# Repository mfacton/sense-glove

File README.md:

# sense-glove
Position Sensing Glove

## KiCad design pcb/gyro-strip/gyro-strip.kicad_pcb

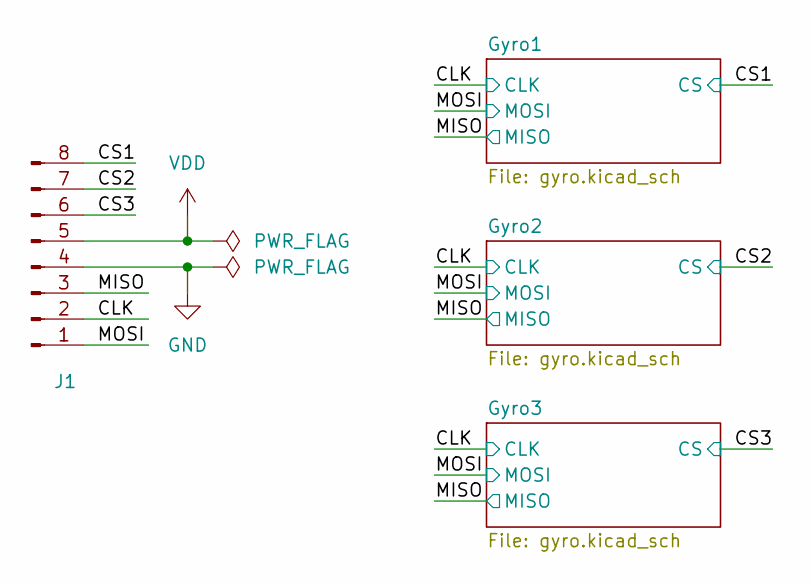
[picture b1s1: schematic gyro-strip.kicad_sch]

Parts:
J1: Conn_01x08_Pin; FPC_8P_P0.5mm

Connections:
/CLK: J1.2; also elsewhere on the board
/CS1: J1.8; also elsewhere on the board
/CS2: J1.7; also elsewhere on the board
/CS3: J1.6; also elsewhere on the board
/MISO: J1.3; also elsewhere on the board
/MOSI: J1.1; also elsewhere on the board
GND: J1.4; also elsewhere on the board
VDD: J1.5; also elsewhere on the board

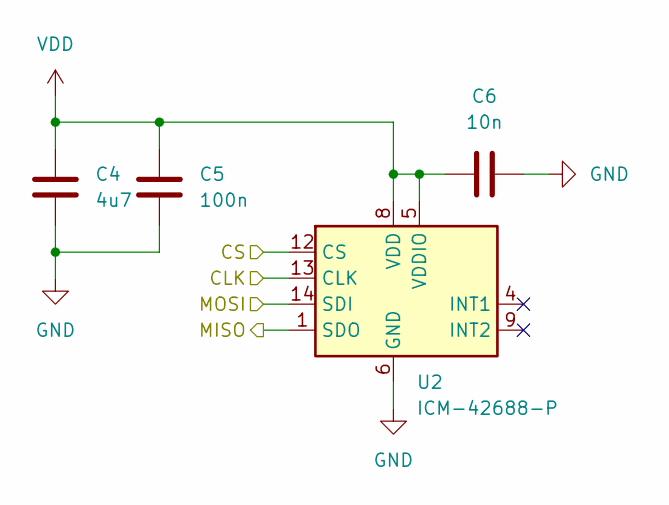
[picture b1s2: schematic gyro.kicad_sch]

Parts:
C4: 4u7; C_0402_1005Metric; LCSC C23733
C5: 100n; C_0402_1005Metric; LCSC C1525
C6: 10n; C_0402_1005Metric; LCSC C15195
U2: ICM-42688-P; LGA-14_3x2.5mm_P0.5mm_LayoutBorder3x4y; LCSC C1850418

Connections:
/CLK: U2.13 (CLK); also elsewhere on the board
/CS2: U2.12 (CS); also elsewhere on the board
/MISO: U2.1 (SDO); also elsewhere on the board
/MOSI: U2.14 (SDI); also elsewhere on the board
GND: C4.2, C5.2, C6.2, U2.6 (GND), U2.7 (RESV), U2.11 (RESV); also elsewhere on the board
VDD: C4.1, C5.1, C6.1, U2.5 (VDDIO), U2.8 (VDD); also elsewhere on the board

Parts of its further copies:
C1, C7: 4u7; C_0402_1005Metric; LCSC C23733
C2, C8: 100n; C_0402_1005Metric; LCSC C1525
C3, C9: 10n; C_0402_1005Metric; LCSC C15195
U1, U3: ICM-42688-P; LGA-14_3x2.5mm_P0.5mm_LayoutBorder3x4y; LCSC C1850418

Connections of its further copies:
/CLK: U1.13 (CLK), U3.13 (CLK); also elsewhere on the board
/CS1: U1.12 (CS); also elsewhere on the board
/CS3: U3.12 (CS); also elsewhere on the board
/MISO: U1.1 (SDO), U3.1 (SDO); also elsewhere on the board
/MOSI: U1.14 (SDI), U3.14 (SDI); also elsewhere on the board
GND: C1.2, C2.2, C3.2, C7.2, C8.2, C9.2, U1.6 (GND), U1.7 (RESV), U1.11 (RESV), U3.6 (GND), U3.7 (RESV), U3.11 (RESV); also elsewhere on the board
VDD: C1.1, C2.1, C3.1, C7.1, C8.1, C9.1, U1.5 (VDDIO), U1.8 (VDD), U3.5 (VDDIO), U3.8 (VDD); also elsewhere on the board

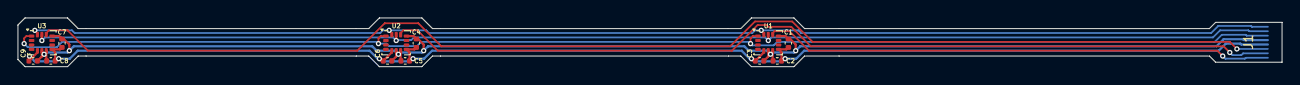
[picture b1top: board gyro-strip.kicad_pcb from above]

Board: 2 copper layers, 142.7 x 5.5 mm, 13 parts (0 on the bottom side), 8 nets.

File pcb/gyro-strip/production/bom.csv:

Designator,Footprint,Quantity,Value,LCSC Part #
"C1, C4, C7",0402,3,4u7,C23733
"C2, C5, C8",0402,3,100n,C1525
"C3, C6, C9",0402,3,10n,C15195
J1,FPC_8P_P0.5mm,1,Conn_01x08_Pin,
"U1, U2, U3",LGA-14_3x2.5mm_P0.5mm_LayoutBorder3x4y,3,ICM-42688-P,C1850418

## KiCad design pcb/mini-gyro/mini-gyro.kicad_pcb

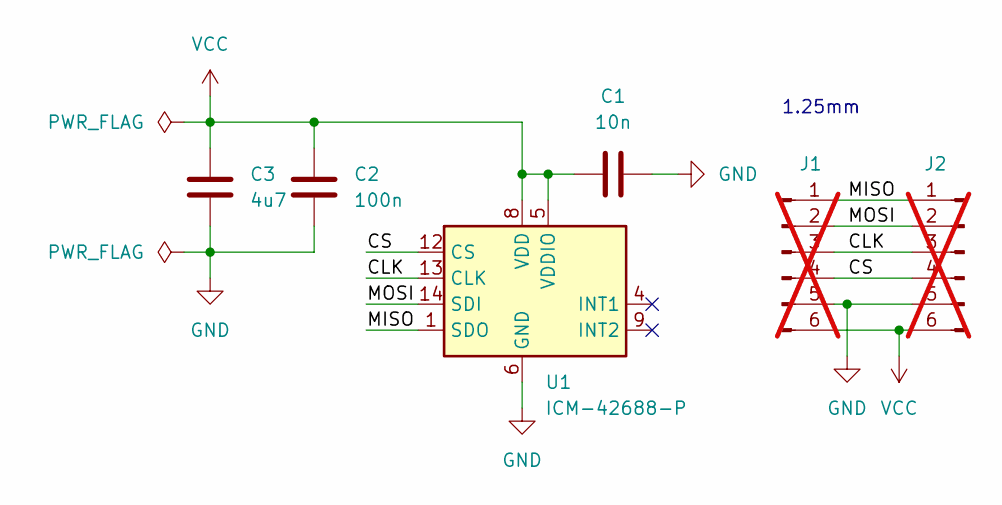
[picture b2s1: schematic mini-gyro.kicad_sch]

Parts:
C1: 10n; C_0402_1005Metric; LCSC C15195
C2: 100n; C_0402_1005Metric; LCSC C1525
C3: 4u7; C_0402_1005Metric; LCSC C23733
J1, J2: Conn_01x06_Pin; PinHeader_1x06_P1.00mm_Vertical; not fitted
U1: ICM-42688-P; LGA-14_3x2.5mm_P0.5mm_LayoutBorder3x4y; LCSC C1850418

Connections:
/CLK: J1.3, J2.3, U1.13 (CLK)
/CS: J1.4, J2.4, U1.12 (CS)
/MISO: J1.1, J2.1, U1.1 (SDO)
/MOSI: J1.2, J2.2, U1.14 (SDI)
GND: C1.2, C2.2, C3.2, J1.5, J2.5, U1.6 (GND), U1.7 (RESV), U1.11 (RESV)
VCC: C1.1, C2.1, C3.1, J1.6, J2.6, U1.5 (VDDIO), U1.8 (VDD)

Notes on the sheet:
1.25mm

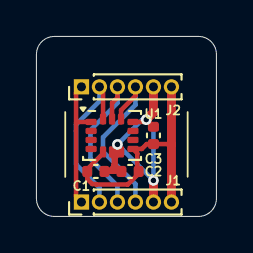
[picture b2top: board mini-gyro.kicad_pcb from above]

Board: 2 copper layers, 10.0 x 10.0 mm, 6 parts (0 on the bottom side), 6 nets.

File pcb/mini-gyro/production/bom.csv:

Designator,Footprint,Quantity,Value,LCSC Part #
C1,0402,1,10n,C15195
C2,0402,1,100n,C1525
C3,0402,1,4u7,C23733
U1,LGA-14_3x2.5mm_P0.5mm_LayoutBorder3x4y,1,ICM-42688-P,C1850418

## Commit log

2024-07-07 Add gitignores
2024-07-15 Make bigger for assembly test run
2024-09-04 Finish gyro strip
2024-09-04 Save project planning
